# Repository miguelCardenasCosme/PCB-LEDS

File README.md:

# LEDs Payload PCB

LED array PCB for the optical downlink payload of the TEIDESAT-1 CubeSat.
The board emits modulated light pulses towards ground stations.

## Status

**v0.3** — layout complete, ready for manufacturing.
This version is intended to validate the predictions of the satellite's
transient thermal study.

## Design summary

- **LEDs:** 260 LEDs in 65 groups of 4 in series (12 V per group).
  Group placement was generated with an automated packing script,
  using line, L, Z, T and square group shapes.
- **Stackup (4 layers, top to bottom):** driver connectors / GND / 12V / LEDs.
- **Power distribution:** copper zones instead of tracks.
- **Vias:** through vias (blind vias were not available in the manufacturing process).
- **Connectors:** 5-pin (4-pin parts were out of stock). Required current capacity: 23 A.
- **Central opening:** leaves room for the optical board mounted behind.
- The LED driver is a separate PCB; it connects to this board through global connectors.

## Repository structure

- `hardware/` — KiCad project (schematic, PCB, project file and custom symbol/footprint/3D libraries).

Open with **KiCad 10.0.5** or newer.

## Open items / future versions

- Thermal: no copper changes for heat dissipation in v0.3. The board is planned
  to be mounted on an aluminium plate; check the risk of shorts through the through vias.

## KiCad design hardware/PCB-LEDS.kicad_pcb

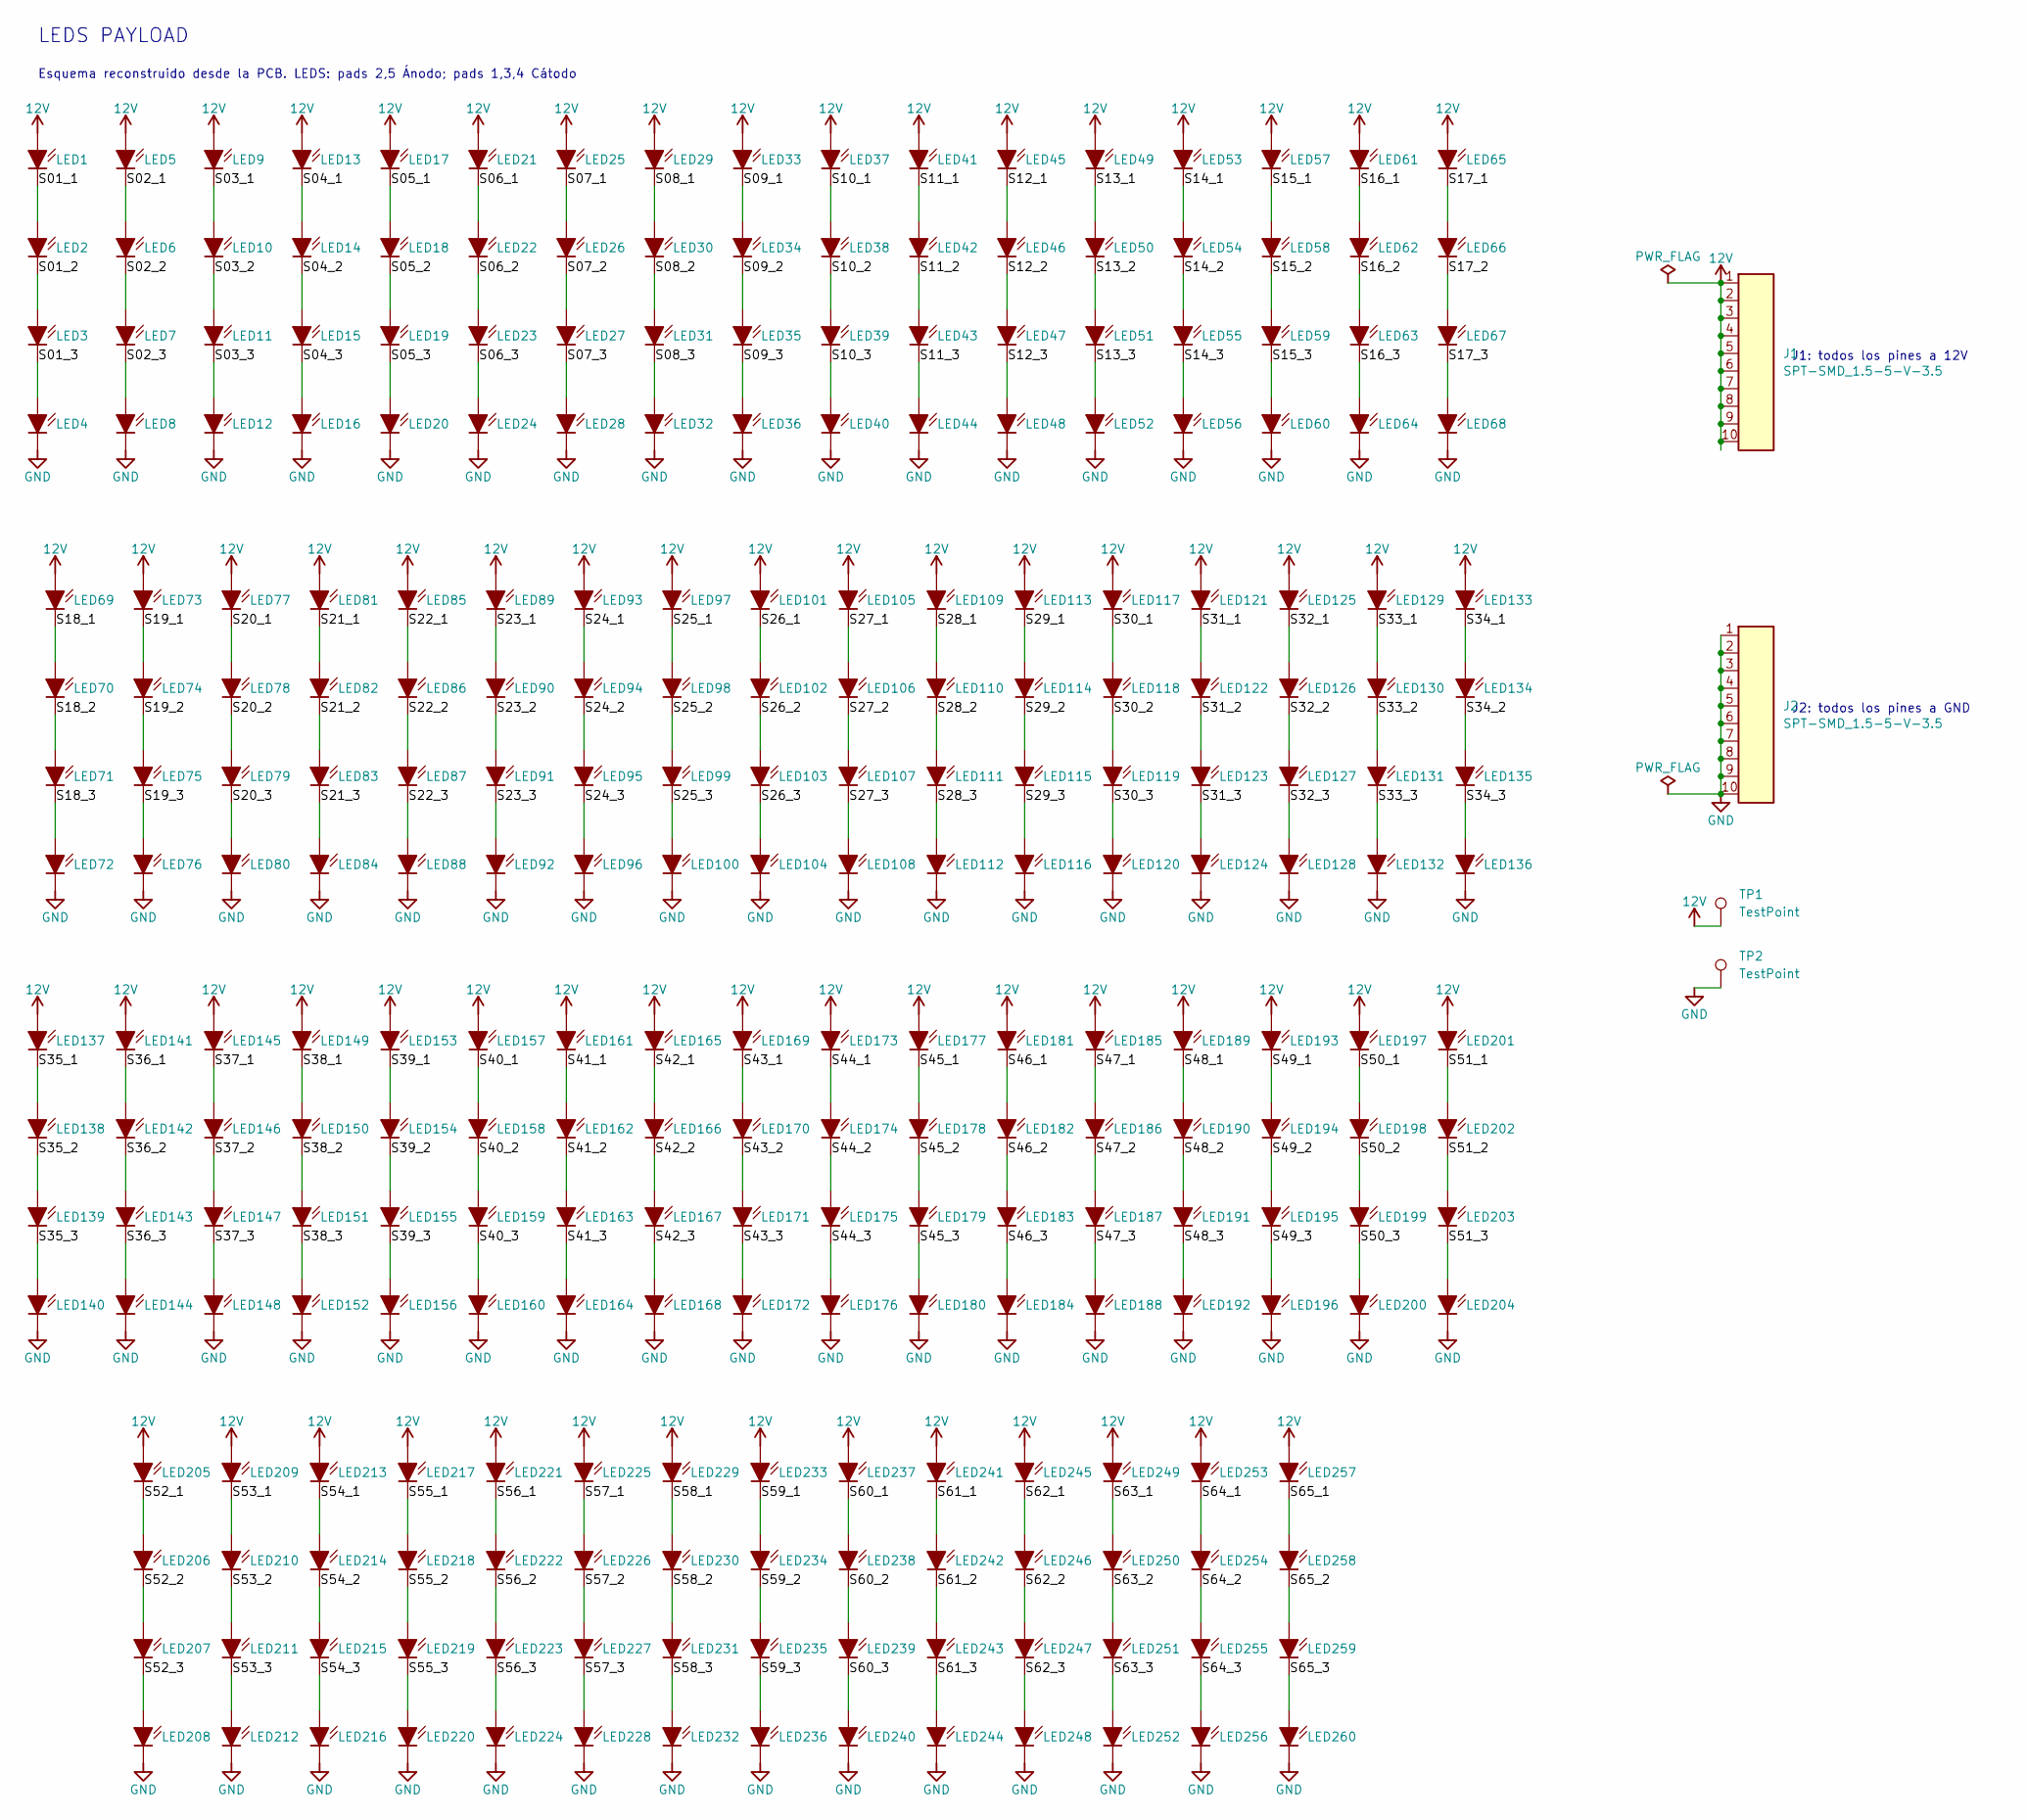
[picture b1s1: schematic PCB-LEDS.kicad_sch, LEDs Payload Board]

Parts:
J1, J2: SPT-SMD_1.5-5-V-3.5
LED1, LED2, LED3, LED4, LED5, LED6, LED7, LED8, LED9, LED10, LED11, LED12, LED13, LED14, LED15, LED16, LED17, LED18, LED19, LED20, LED21, LED22, LED23, LED24, LED25, LED26, LED27, LED28, LED29, LED30, LED31, LED32, LED33, LED34, LED35, LED36, LED37, LED38, LED39, LED40, LED41, LED42, LED43, LED44, LED45, LED46, LED47, LED48, LED49, LED50, LED51, LED52, LED53, LED54, LED55, LED56, LED57, LED58, LED59, LED60, LED61, LED62, LED63, LED64, LED65, LED66, LED67, LED68, LED69, LED70, LED71, LED72, LED73, LED74, LED75, LED76, LED77, LED78, LED79, LED80, LED81, LED82, LED83, LED84, LED85, LED86, LED87, LED88, LED89, LED90, LED91, LED92, LED93, LED94, LED95, LED96, LED97, LED98, LED99, LED100, LED101, LED102, LED103, LED104, LED105, LED106, LED107, LED108, LED109, LED110, LED111, LED112, LED113, LED114, LED115, LED116, LED117, LED118, LED119, LED120, LED121, LED122, LED123, LED124, LED125, LED126, LED127, LED128, LED129, LED130, LED131, LED132, LED133, LED134, LED135, LED136, LED137, LED138, LED139, LED140, LED141, LED142, LED143, LED144, LED145, LED146, LED147, LED148, LED149, LED150, LED151, LED152, LED153, LED154, LED155, LED156, LED157, LED158, LED159, LED160, LED161, LED162, LED163, LED164, LED165, LED166, LED167, LED168, LED169, LED170, LED171, LED172, LED173, LED174, LED175, LED176, LED177, LED178, LED179, LED180, LED181, LED182, LED183, LED184, LED185, LED186, LED187, LED188, LED189, LED190, LED191, LED192, LED193, LED194, LED195, LED196, LED197, LED198, LED199, LED200, LED201, LED202, LED203, LED204, LED205, LED206, LED207, LED208, LED209, LED210, LED211, LED212, LED213, LED214, LED215, LED216, LED217, LED218, LED219, LED220, LED221, LED222, LED223, LED224, LED225, LED226, LED227, LED228, LED229, LED230, LED231, LED232, LED233, LED234, LED235, LED236, LED237, LED238, LED239, LED240, LED241, LED242, LED243, LED244, LED245, LED246, LED247, LED248, LED249, LED250, LED251, LED252, LED253, LED254, LED255, LED256, LED257, LED258, LED259, LED260: KW_DMLQ33.SG
TP1, TP2: TestPoint; TestPoint_Pad_D1.5mm

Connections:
12V: J1.1, J1.2, J1.3, J1.4, J1.5, J1.6, J1.7, J1.8, J1.9, J1.10, LED1.2 (A), LED1.5 (A), LED5.2 (A), LED5.5 (A), LED9.2 (A), LED9.5 (A), LED13.2 (A), LED13.5 (A), LED17.2 (A), LED17.5 (A), LED21.2 (A), LED21.5 (A), LED25.2 (A), LED25.5 (A), LED29.2 (A), LED29.5 (A), LED33.2 (A), LED33.5 (A), LED37.2 (A), LED37.5 (A), LED41.2 (A), LED41.5 (A), LED45.2 (A), LED45.5 (A), LED49.2 (A), LED49.5 (A), LED53.2 (A), LED53.5 (A), LED57.2 (A), LED57.5 (A), LED61.2 (A), LED61.5 (A), LED65.2 (A), LED65.5 (A), LED69.2 (A), LED69.5 (A), LED73.2 (A), LED73.5 (A), LED77.2 (A), LED77.5 (A), LED81.2 (A), LED81.5 (A), LED85.2 (A), LED85.5 (A), LED89.2 (A), LED89.5 (A), LED93.2 (A), LED93.5 (A), LED97.2 (A), LED97.5 (A), LED101.2 (A), LED101.5 (A), LED105.2 (A), LED105.5 (A), LED109.2 (A), LED109.5 (A), LED113.2 (A), LED113.5 (A), LED117.2 (A), LED117.5 (A), LED121.2 (A), LED121.5 (A), LED125.2 (A), LED125.5 (A), LED129.2 (A), LED129.5 (A), LED133.2 (A), LED133.5 (A), LED137.2 (A), LED137.5 (A), LED141.2 (A), LED141.5 (A), LED145.2 (A), LED145.5 (A), LED149.2 (A), LED149.5 (A), LED153.2 (A), LED153.5 (A), LED157.2 (A), LED157.5 (A), LED161.2 (A), LED161.5 (A), LED165.2 (A), LED165.5 (A), LED169.2 (A), LED169.5 (A), LED173.2 (A), LED173.5 (A), LED177.2 (A), LED177.5 (A), LED181.2 (A), LED181.5 (A), LED185.2 (A), LED185.5 (A), LED189.2 (A), LED189.5 (A), LED193.2 (A), LED193.5 (A), LED197.2 (A), LED197.5 (A), LED201.2 (A), LED201.5 (A), LED205.2 (A), LED205.5 (A), LED209.2 (A), LED209.5 (A), LED213.2 (A), LED213.5 (A), LED217.2 (A), LED217.5 (A), LED221.2 (A), LED221.5 (A), LED225.2 (A), LED225.5 (A), LED229.2 (A), LED229.5 (A), LED233.2 (A), LED233.5 (A), LED237.2 (A), LED237.5 (A), LED241.2 (A), LED241.5 (A), LED245.2 (A), LED245.5 (A), LED249.2 (A), LED249.5 (A), LED253.2 (A), LED253.5 (A), LED257.2 (A), LED257.5 (A), TP1.1 (1_1)
/S01_1: LED1.1 (K), LED1.3 (K), LED1.4 (K), LED2.2 (A), LED2.5 (A)
/S01_2: LED2.1 (K), LED2.3 (K), LED2.4 (K), LED3.2 (A), LED3.5 (A)
/S01_3: LED3.1 (K), LED3.3 (K), LED3.4 (K), LED4.2 (A), LED4.5 (A)
/S02_1: LED5.1 (K), LED5.3 (K), LED5.4 (K), LED6.2 (A), LED6.5 (A)
/S02_2: LED6.1 (K), LED6.3 (K), LED6.4 (K), LED7.2 (A), LED7.5 (A)
/S02_3: LED7.1 (K), LED7.3 (K), LED7.4 (K), LED8.2 (A), LED8.5 (A)
/S03_1: LED9.1 (K), LED9.3 (K), LED9.4 (K), LED10.2 (A), LED10.5 (A)
/S03_2: LED10.1 (K), LED10.3 (K), LED10.4 (K), LED11.2 (A), LED11.5 (A)
/S03_3: LED11.1 (K), LED11.3 (K), LED11.4 (K), LED12.2 (A), LED12.5 (A)
/S04_1: LED13.1 (K), LED13.3 (K), LED13.4 (K), LED14.2 (A), LED14.5 (A)
/S04_2: LED14.1 (K), LED14.3 (K), LED14.4 (K), LED15.2 (A), LED15.5 (A)
/S04_3: LED15.1 (K), LED15.3 (K), LED15.4 (K), LED16.2 (A), LED16.5 (A)
/S05_1: LED17.1 (K), LED17.3 (K), LED17.4 (K), LED18.2 (A), LED18.5 (A)
/S05_2: LED18.1 (K), LED18.3 (K), LED18.4 (K), LED19.2 (A), LED19.5 (A)
/S05_3: LED19.1 (K), LED19.3 (K), LED19.4 (K), LED20.2 (A), LED20.5 (A)
/S06_1: LED21.1 (K), LED21.3 (K), LED21.4 (K), LED22.2 (A), LED22.5 (A)
/S06_2: LED22.1 (K), LED22.3 (K), LED22.4 (K), LED23.2 (A), LED23.5 (A)
/S06_3: LED23.1 (K), LED23.3 (K), LED23.4 (K), LED24.2 (A), LED24.5 (A)
/S07_1: LED25.1 (K), LED25.3 (K), LED25.4 (K), LED26.2 (A), LED26.5 (A)
/S07_2: LED26.1 (K), LED26.3 (K), LED26.4 (K), LED27.2 (A), LED27.5 (A)
/S07_3: LED27.1 (K), LED27.3 (K), LED27.4 (K), LED28.2 (A), LED28.5 (A)
/S08_1: LED29.1 (K), LED29.3 (K), LED29.4 (K), LED30.2 (A), LED30.5 (A)
/S08_2: LED30.1 (K), LED30.3 (K), LED30.4 (K), LED31.2 (A), LED31.5 (A)
/S08_3: LED31.1 (K), LED31.3 (K), LED31.4 (K), LED32.2 (A), LED32.5 (A)
/S09_1: LED33.1 (K), LED33.3 (K), LED33.4 (K), LED34.2 (A), LED34.5 (A)
/S09_2: LED34.1 (K), LED34.3 (K), LED34.4 (K), LED35.2 (A), LED35.5 (A)
/S09_3: LED35.1 (K), LED35.3 (K), LED35.4 (K), LED36.2 (A), LED36.5 (A)
/S10_1: LED37.1 (K), LED37.3 (K), LED37.4 (K), LED38.2 (A), LED38.5 (A)
/S10_2: LED38.1 (K), LED38.3 (K), LED38.4 (K), LED39.2 (A), LED39.5 (A)
/S10_3: LED39.1 (K), LED39.3 (K), LED39.4 (K), LED40.2 (A), LED40.5 (A)
/S11_1: LED41.1 (K), LED41.3 (K), LED41.4 (K), LED42.2 (A), LED42.5 (A)
/S11_2: LED42.1 (K), LED42.3 (K), LED42.4 (K), LED43.2 (A), LED43.5 (A)
/S11_3: LED43.1 (K), LED43.3 (K), LED43.4 (K), LED44.2 (A), LED44.5 (A)
/S12_1: LED45.1 (K), LED45.3 (K), LED45.4 (K), LED46.2 (A), LED46.5 (A)
/S12_2: LED46.1 (K), LED46.3 (K), LED46.4 (K), LED47.2 (A), LED47.5 (A)
/S12_3: LED47.1 (K), LED47.3 (K), LED47.4 (K), LED48.2 (A), LED48.5 (A)
/S13_1: LED49.1 (K), LED49.3 (K), LED49.4 (K), LED50.2 (A), LED50.5 (A)
/S13_2: LED50.1 (K), LED50.3 (K), LED50.4 (K), LED51.2 (A), LED51.5 (A)
/S13_3: LED51.1 (K), LED51.3 (K), LED51.4 (K), LED52.2 (A), LED52.5 (A)
/S14_1: LED53.1 (K), LED53.3 (K), LED53.4 (K), LED54.2 (A), LED54.5 (A)
/S14_2: LED54.1 (K), LED54.3 (K), LED54.4 (K), LED55.2 (A), LED55.5 (A)
/S14_3: LED55.1 (K), LED55.3 (K), LED55.4 (K), LED56.2 (A), LED56.5 (A)
/S15_1: LED57.1 (K), LED57.3 (K), LED57.4 (K), LED58.2 (A), LED58.5 (A)
/S15_2: LED58.1 (K), LED58.3 (K), LED58.4 (K), LED59.2 (A), LED59.5 (A)
/S15_3: LED59.1 (K), LED59.3 (K), LED59.4 (K), LED60.2 (A), LED60.5 (A)
/S16_1: LED61.1 (K), LED61.3 (K), LED61.4 (K), LED62.2 (A), LED62.5 (A)
/S16_2: LED62.1 (K), LED62.3 (K), LED62.4 (K), LED63.2 (A), LED63.5 (A)
/S16_3: LED63.1 (K), LED63.3 (K), LED63.4 (K), LED64.2 (A), LED64.5 (A)
/S17_1: LED65.1 (K), LED65.3 (K), LED65.4 (K), LED66.2 (A), LED66.5 (A)
/S17_2: LED66.1 (K), LED66.3 (K), LED66.4 (K), LED67.2 (A), LED67.5 (A)
/S17_3: LED67.1 (K), LED67.3 (K), LED67.4 (K), LED68.2 (A), LED68.5 (A)
/S18_1: LED69.1 (K), LED69.3 (K), LED69.4 (K), LED70.2 (A), LED70.5 (A)
/S18_2: LED70.1 (K), LED70.3 (K), LED70.4 (K), LED71.2 (A), LED71.5 (A)
/S18_3: LED71.1 (K), LED71.3 (K), LED71.4 (K), LED72.2 (A), LED72.5 (A)
/S19_1: LED73.1 (K), LED73.3 (K), LED73.4 (K), LED74.2 (A), LED74.5 (A)
/S19_2: LED74.1 (K), LED74.3 (K), LED74.4 (K), LED75.2 (A), LED75.5 (A)
/S19_3: LED75.1 (K), LED75.3 (K), LED75.4 (K), LED76.2 (A), LED76.5 (A)
/S20_1: LED77.1 (K), LED77.3 (K), LED77.4 (K), LED78.2 (A), LED78.5 (A)
/S20_2: LED78.1 (K), LED78.3 (K), LED78.4 (K), LED79.2 (A), LED79.5 (A)
/S20_3: LED79.1 (K), LED79.3 (K), LED79.4 (K), LED80.2 (A), LED80.5 (A)
/S21_1: LED81.1 (K), LED81.3 (K), LED81.4 (K), LED82.2 (A), LED82.5 (A)
/S21_2: LED82.1 (K), LED82.3 (K), LED82.4 (K), LED83.2 (A), LED83.5 (A)
/S21_3: LED83.1 (K), LED83.3 (K), LED83.4 (K), LED84.2 (A), LED84.5 (A)
/S22_1: LED85.1 (K), LED85.3 (K), LED85.4 (K), LED86.2 (A), LED86.5 (A)
/S22_2: LED86.1 (K), LED86.3 (K), LED86.4 (K), LED87.2 (A), LED87.5 (A)
/S22_3: LED87.1 (K), LED87.3 (K), LED87.4 (K), LED88.2 (A), LED88.5 (A)
/S23_1: LED89.1 (K), LED89.3 (K), LED89.4 (K), LED90.2 (A), LED90.5 (A)
/S23_2: LED90.1 (K), LED90.3 (K), LED90.4 (K), LED91.2 (A), LED91.5 (A)
/S23_3: LED91.1 (K), LED91.3 (K), LED91.4 (K), LED92.2 (A), LED92.5 (A)
/S24_1: LED93.1 (K), LED93.3 (K), LED93.4 (K), LED94.2 (A), LED94.5 (A)
/S24_2: LED94.1 (K), LED94.3 (K), LED94.4 (K), LED95.2 (A), LED95.5 (A)
/S24_3: LED95.1 (K), LED95.3 (K), LED95.4 (K), LED96.2 (A), LED96.5 (A)
/S25_1: LED97.1 (K), LED97.3 (K), LED97.4 (K), LED98.2 (A), LED98.5 (A)
/S25_2: LED98.1 (K), LED98.3 (K), LED98.4 (K), LED99.2 (A), LED99.5 (A)
/S25_3: LED99.1 (K), LED99.3 (K), LED99.4 (K), LED100.2 (A), LED100.5 (A)
/S26_1: LED101.1 (K), LED101.3 (K), LED101.4 (K), LED102.2 (A), LED102.5 (A)
/S26_2: LED102.1 (K), LED102.3 (K), LED102.4 (K), LED103.2 (A), LED103.5 (A)
/S26_3: LED103.1 (K), LED103.3 (K), LED103.4 (K), LED104.2 (A), LED104.5 (A)
/S27_1: LED105.1 (K), LED105.3 (K), LED105.4 (K), LED106.2 (A), LED106.5 (A)
/S27_2: LED106.1 (K), LED106.3 (K), LED106.4 (K), LED107.2 (A), LED107.5 (A)
/S27_3: LED107.1 (K), LED107.3 (K), LED107.4 (K), LED108.2 (A), LED108.5 (A)
/S28_1: LED109.1 (K), LED109.3 (K), LED109.4 (K), LED110.2 (A), LED110.5 (A)
/S28_2: LED110.1 (K), LED110.3 (K), LED110.4 (K), LED111.2 (A), LED111.5 (A)
/S28_3: LED111.1 (K), LED111.3 (K), LED111.4 (K), LED112.2 (A), LED112.5 (A)
/S29_1: LED113.1 (K), LED113.3 (K), LED113.4 (K), LED114.2 (A), LED114.5 (A)
/S29_2: LED114.1 (K), LED114.3 (K), LED114.4 (K), LED115.2 (A), LED115.5 (A)
/S29_3: LED115.1 (K), LED115.3 (K), LED115.4 (K), LED116.2 (A), LED116.5 (A)
/S30_1: LED117.1 (K), LED117.3 (K), LED117.4 (K), LED118.2 (A), LED118.5 (A)
/S30_2: LED118.1 (K), LED118.3 (K), LED118.4 (K), LED119.2 (A), LED119.5 (A)
/S30_3: LED119.1 (K), LED119.3 (K), LED119.4 (K), LED120.2 (A), LED120.5 (A)
/S31_1: LED121.1 (K), LED121.3 (K), LED121.4 (K), LED122.2 (A), LED122.5 (A)
/S31_2: LED122.1 (K), LED122.3 (K), LED122.4 (K), LED123.2 (A), LED123.5 (A)
/S31_3: LED123.1 (K), LED123.3 (K), LED123.4 (K), LED124.2 (A), LED124.5 (A)
/S32_1: LED125.1 (K), LED125.3 (K), LED125.4 (K), LED126.2 (A), LED126.5 (A)
/S32_2: LED126.1 (K), LED126.3 (K), LED126.4 (K), LED127.2 (A), LED127.5 (A)
/S32_3: LED127.1 (K), LED127.3 (K), LED127.4 (K), LED128.2 (A), LED128.5 (A)
/S33_1: LED129.1 (K), LED129.3 (K), LED129.4 (K), LED130.2 (A), LED130.5 (A)
/S33_2: LED130.1 (K), LED130.3 (K), LED130.4 (K), LED131.2 (A), LED131.5 (A)
/S33_3: LED131.1 (K), LED131.3 (K), LED131.4 (K), LED132.2 (A), LED132.5 (A)
/S34_1: LED133.1 (K), LED133.3 (K), LED133.4 (K), LED134.2 (A), LED134.5 (A)
/S34_2: LED134.1 (K), LED134.3 (K), LED134.4 (K), LED135.2 (A), LED135.5 (A)
/S34_3: LED135.1 (K), LED135.3 (K), LED135.4 (K), LED136.2 (A), LED136.5 (A)
/S35_1: LED137.1 (K), LED137.3 (K), LED137.4 (K), LED138.2 (A), LED138.5 (A)
/S35_2: LED138.1 (K), LED138.3 (K), LED138.4 (K), LED139.2 (A), LED139.5 (A)
/S35_3: LED139.1 (K), LED139.3 (K), LED139.4 (K), LED140.2 (A), LED140.5 (A)
/S36_1: LED141.1 (K), LED141.3 (K), LED141.4 (K), LED142.2 (A), LED142.5 (A)
/S36_2: LED142.1 (K), LED142.3 (K), LED142.4 (K), LED143.2 (A), LED143.5 (A)
/S36_3: LED143.1 (K), LED143.3 (K), LED143.4 (K), LED144.2 (A), LED144.5 (A)
/S37_1: LED145.1 (K), LED145.3 (K), LED145.4 (K), LED146.2 (A), LED146.5 (A)
/S37_2: LED146.1 (K), LED146.3 (K), LED146.4 (K), LED147.2 (A), LED147.5 (A)
/S37_3: LED147.1 (K), LED147.3 (K), LED147.4 (K), LED148.2 (A), LED148.5 (A)
/S38_1: LED149.1 (K), LED149.3 (K), LED149.4 (K), LED150.2 (A), LED150.5 (A)
/S38_2: LED150.1 (K), LED150.3 (K), LED150.4 (K), LED151.2 (A), LED151.5 (A)
/S38_3: LED151.1 (K), LED151.3 (K), LED151.4 (K), LED152.2 (A), LED152.5 (A)
/S39_1: LED153.1 (K), LED153.3 (K), LED153.4 (K), LED154.2 (A), LED154.5 (A)
/S39_2: LED154.1 (K), LED154.3 (K), LED154.4 (K), LED155.2 (A), LED155.5 (A)
/S39_3: LED155.1 (K), LED155.3 (K), LED155.4 (K), LED156.2 (A), LED156.5 (A)
/S40_1: LED157.1 (K), LED157.3 (K), LED157.4 (K), LED158.2 (A), LED158.5 (A)
/S40_2: LED158.1 (K), LED158.3 (K), LED158.4 (K), LED159.2 (A), LED159.5 (A)
/S40_3: LED159.1 (K), LED159.3 (K), LED159.4 (K), LED160.2 (A), LED160.5 (A)
/S41_1: LED161.1 (K), LED161.3 (K), LED161.4 (K), LED162.2 (A), LED162.5 (A)
/S41_2: LED162.1 (K), LED162.3 (K), LED162.4 (K), LED163.2 (A), LED163.5 (A)
/S41_3: LED163.1 (K), LED163.3 (K), LED163.4 (K), LED164.2 (A), LED164.5 (A)
/S42_1: LED165.1 (K), LED165.3 (K), LED165.4 (K), LED166.2 (A), LED166.5 (A)
/S42_2: LED166.1 (K), LED166.3 (K), LED166.4 (K), LED167.2 (A), LED167.5 (A)
/S42_3: LED167.1 (K), LED167.3 (K), LED167.4 (K), LED168.2 (A), LED168.5 (A)
/S43_1: LED169.1 (K), LED169.3 (K), LED169.4 (K), LED170.2 (A), LED170.5 (A)
/S43_2: LED170.1 (K), LED170.3 (K), LED170.4 (K), LED171.2 (A), LED171.5 (A)
/S43_3: LED171.1 (K), LED171.3 (K), LED171.4 (K), LED172.2 (A), LED172.5 (A)
/S44_1: LED173.1 (K), LED173.3 (K), LED173.4 (K), LED174.2 (A), LED174.5 (A)
/S44_2: LED174.1 (K), LED174.3 (K), LED174.4 (K), LED175.2 (A), LED175.5 (A)
/S44_3: LED175.1 (K), LED175.3 (K), LED175.4 (K), LED176.2 (A), LED176.5 (A)
/S45_1: LED177.1 (K), LED177.3 (K), LED177.4 (K), LED178.2 (A), LED178.5 (A)
/S45_2: LED178.1 (K), LED178.3 (K), LED178.4 (K), LED179.2 (A), LED179.5 (A)
/S45_3: LED179.1 (K), LED179.3 (K), LED179.4 (K), LED180.2 (A), LED180.5 (A)
/S46_1: LED181.1 (K), LED181.3 (K), LED181.4 (K), LED182.2 (A), LED182.5 (A)
/S46_2: LED182.1 (K), LED182.3 (K), LED182.4 (K), LED183.2 (A), LED183.5 (A)
/S46_3: LED183.1 (K), LED183.3 (K), LED183.4 (K), LED184.2 (A), LED184.5 (A)
/S47_1: LED185.1 (K), LED185.3 (K), LED185.4 (K), LED186.2 (A), LED186.5 (A)
/S47_2: LED186.1 (K), LED186.3 (K), LED186.4 (K), LED187.2 (A), LED187.5 (A)
/S47_3: LED187.1 (K), LED187.3 (K), LED187.4 (K), LED188.2 (A), LED188.5 (A)
/S48_1: LED189.1 (K), LED189.3 (K), LED189.4 (K), LED190.2 (A), LED190.5 (A)
/S48_2: LED190.1 (K), LED190.3 (K), LED190.4 (K), LED191.2 (A), LED191.5 (A)
/S48_3: LED191.1 (K), LED191.3 (K), LED191.4 (K), LED192.2 (A), LED192.5 (A)
/S49_1: LED193.1 (K), LED193.3 (K), LED193.4 (K), LED194.2 (A), LED194.5 (A)
/S49_2: LED194.1 (K), LED194.3 (K), LED194.4 (K), LED195.2 (A), LED195.5 (A)
/S49_3: LED195.1 (K), LED195.3 (K), LED195.4 (K), LED196.2 (A), LED196.5 (A)
/S50_1: LED197.1 (K), LED197.3 (K), LED197.4 (K), LED198.2 (A), LED198.5 (A)
/S50_2: LED198.1 (K), LED198.3 (K), LED198.4 (K), LED199.2 (A), LED199.5 (A)
/S50_3: LED199.1 (K), LED199.3 (K), LED199.4 (K), LED200.2 (A), LED200.5 (A)
/S51_1: LED201.1 (K), LED201.3 (K), LED201.4 (K), LED202.2 (A), LED202.5 (A)
/S51_2: LED202.1 (K), LED202.3 (K), LED202.4 (K), LED203.2 (A), LED203.5 (A)
/S51_3: LED203.1 (K), LED203.3 (K), LED203.4 (K), LED204.2 (A), LED204.5 (A)
/S52_1: LED205.1 (K), LED205.3 (K), LED205.4 (K), LED206.2 (A), LED206.5 (A)
/S52_2: LED206.1 (K), LED206.3 (K), LED206.4 (K), LED207.2 (A), LED207.5 (A)
/S52_3: LED207.1 (K), LED207.3 (K), LED207.4 (K), LED208.2 (A), LED208.5 (A)
/S53_1: LED209.1 (K), LED209.3 (K), LED209.4 (K), LED210.2 (A), LED210.5 (A)
/S53_2: LED210.1 (K), LED210.3 (K), LED210.4 (K), LED211.2 (A), LED211.5 (A)
/S53_3: LED211.1 (K), LED211.3 (K), LED211.4 (K), LED212.2 (A), LED212.5 (A)
/S54_1: LED213.1 (K), LED213.3 (K), LED213.4 (K), LED214.2 (A), LED214.5 (A)
/S54_2: LED214.1 (K), LED214.3 (K), LED214.4 (K), LED215.2 (A), LED215.5 (A)
/S54_3: LED215.1 (K), LED215.3 (K), LED215.4 (K), LED216.2 (A), LED216.5 (A)
/S55_1: LED217.1 (K), LED217.3 (K), LED217.4 (K), LED218.2 (A), LED218.5 (A)
/S55_2: LED218.1 (K), LED218.3 (K), LED218.4 (K), LED219.2 (A), LED219.5 (A)
/S55_3: LED219.1 (K), LED219.3 (K), LED219.4 (K), LED220.2 (A), LED220.5 (A)
/S56_1: LED221.1 (K), LED221.3 (K), LED221.4 (K), LED222.2 (A), LED222.5 (A)
/S56_2: LED222.1 (K), LED222.3 (K), LED222.4 (K), LED223.2 (A), LED223.5 (A)
/S56_3: LED223.1 (K), LED223.3 (K), LED223.4 (K), LED224.2 (A), LED224.5 (A)
/S57_1: LED225.1 (K), LED225.3 (K), LED225.4 (K), LED226.2 (A), LED226.5 (A)
/S57_2: LED226.1 (K), LED226.3 (K), LED226.4 (K), LED227.2 (A), LED227.5 (A)
/S57_3: LED227.1 (K), LED227.3 (K), LED227.4 (K), LED228.2 (A), LED228.5 (A)
/S58_1: LED229.1 (K), LED229.3 (K), LED229.4 (K), LED230.2 (A), LED230.5 (A)
/S58_2: LED230.1 (K), LED230.3 (K), LED230.4 (K), LED231.2 (A), LED231.5 (A)
/S58_3: LED231.1 (K), LED231.3 (K), LED231.4 (K), LED232.2 (A), LED232.5 (A)
/S59_1: LED233.1 (K), LED233.3 (K), LED233.4 (K), LED234.2 (A), LED234.5 (A)
/S59_2: LED234.1 (K), LED234.3 (K), LED234.4 (K), LED235.2 (A), LED235.5 (A)
/S59_3: LED235.1 (K), LED235.3 (K), LED235.4 (K), LED236.2 (A), LED236.5 (A)
/S60_1: LED237.1 (K), LED237.3 (K), LED237.4 (K), LED238.2 (A), LED238.5 (A)
/S60_2: LED238.1 (K), LED238.3 (K), LED238.4 (K), LED239.2 (A), LED239.5 (A)
/S60_3: LED239.1 (K), LED239.3 (K), LED239.4 (K), LED240.2 (A), LED240.5 (A)
/S61_1: LED241.1 (K), LED241.3 (K), LED241.4 (K), LED242.2 (A), LED242.5 (A)
/S61_2: LED242.1 (K), LED242.3 (K), LED242.4 (K), LED243.2 (A), LED243.5 (A)
/S61_3: LED243.1 (K), LED243.3 (K), LED243.4 (K), LED244.2 (A), LED244.5 (A)
/S62_1: LED245.1 (K), LED245.3 (K), LED245.4 (K), LED246.2 (A), LED246.5 (A)
/S62_2: LED246.1 (K), LED246.3 (K), LED246.4 (K), LED247.2 (A), LED247.5 (A)
/S62_3: LED247.1 (K), LED247.3 (K), LED247.4 (K), LED248.2 (A), LED248.5 (A)
/S63_1: LED249.1 (K), LED249.3 (K), LED249.4 (K), LED250.2 (A), LED250.5 (A)
/S63_2: LED250.1 (K), LED250.3 (K), LED250.4 (K), LED251.2 (A), LED251.5 (A)
/S63_3: LED251.1 (K), LED251.3 (K), LED251.4 (K), LED252.2 (A), LED252.5 (A)
/S64_1: LED253.1 (K), LED253.3 (K), LED253.4 (K), LED254.2 (A), LED254.5 (A)
/S64_2: LED254.1 (K), LED254.3 (K), LED254.4 (K), LED255.2 (A), LED255.5 (A)
/S64_3: LED255.1 (K), LED255.3 (K), LED255.4 (K), LED256.2 (A), LED256.5 (A)
/S65_1: LED257.1 (K), LED257.3 (K), LED257.4 (K), LED258.2 (A), LED258.5 (A)
/S65_2: LED258.1 (K), LED258.3 (K), LED258.4 (K), LED259.2 (A), LED259.5 (A)
/S65_3: LED259.1 (K), LED259.3 (K), LED259.4 (K), LED260.2 (A), LED260.5 (A)
GND: J2.1, J2.2, J2.3, J2.4, J2.5, J2.6, J2.7, J2.8, J2.9, J2.10, LED4.1 (K), LED4.3 (K), LED4.4 (K), LED8.1 (K), LED8.3 (K), LED8.4 (K), LED12.1 (K), LED12.3 (K), LED12.4 (K), LED16.1 (K), LED16.3 (K), LED16.4 (K), LED20.1 (K), LED20.3 (K), LED20.4 (K), LED24.1 (K), LED24.3 (K), LED24.4 (K), LED28.1 (K), LED28.3 (K), LED28.4 (K), LED32.1 (K), LED32.3 (K), LED32.4 (K), LED36.1 (K), LED36.3 (K), LED36.4 (K), LED40.1 (K), LED40.3 (K), LED40.4 (K), LED44.1 (K), LED44.3 (K), LED44.4 (K), LED48.1 (K), LED48.3 (K), LED48.4 (K), LED52.1 (K), LED52.3 (K), LED52.4 (K), LED56.1 (K), LED56.3 (K), LED56.4 (K), LED60.1 (K), LED60.3 (K), LED60.4 (K), LED64.1 (K), LED64.3 (K), LED64.4 (K), LED68.1 (K), LED68.3 (K), LED68.4 (K), LED72.1 (K), LED72.3 (K), LED72.4 (K), LED76.1 (K), LED76.3 (K), LED76.4 (K), LED80.1 (K), LED80.3 (K), LED80.4 (K), LED84.1 (K), LED84.3 (K), LED84.4 (K), LED88.1 (K), LED88.3 (K), LED88.4 (K), LED92.1 (K), LED92.3 (K), LED92.4 (K), LED96.1 (K), LED96.3 (K), LED96.4 (K), LED100.1 (K), LED100.3 (K), LED100.4 (K), LED104.1 (K), LED104.3 (K), LED104.4 (K), LED108.1 (K), LED108.3 (K), LED108.4 (K), LED112.1 (K), LED112.3 (K), LED112.4 (K), LED116.1 (K), LED116.3 (K), LED116.4 (K), LED120.1 (K), LED120.3 (K), LED120.4 (K), LED124.1 (K), LED124.3 (K), LED124.4 (K), LED128.1 (K), LED128.3 (K), LED128.4 (K), LED132.1 (K), LED132.3 (K), LED132.4 (K), LED136.1 (K), LED136.3 (K), LED136.4 (K), LED140.1 (K), LED140.3 (K), LED140.4 (K), LED144.1 (K), LED144.3 (K), LED144.4 (K), LED148.1 (K), LED148.3 (K), LED148.4 (K), LED152.1 (K), LED152.3 (K), LED152.4 (K), LED156.1 (K), LED156.3 (K), LED156.4 (K), LED160.1 (K), LED160.3 (K), LED160.4 (K), LED164.1 (K), LED164.3 (K), LED164.4 (K), LED168.1 (K), LED168.3 (K), LED168.4 (K), LED172.1 (K), LED172.3 (K), LED172.4 (K), LED176.1 (K), LED176.3 (K), LED176.4 (K), LED180.1 (K), LED180.3 (K), LED180.4 (K), LED184.1 (K), LED184.3 (K), LED184.4 (K), LED188.1 (K), LED188.3 (K), LED188.4 (K), LED192.1 (K), LED192.3 (K), LED192.4 (K), LED196.1 (K), LED196.3 (K), LED196.4 (K), LED200.1 (K), LED200.3 (K), LED200.4 (K), LED204.1 (K), LED204.3 (K), LED204.4 (K), LED208.1 (K), LED208.3 (K), LED208.4 (K), LED212.1 (K), LED212.3 (K), LED212.4 (K), LED216.1 (K), LED216.3 (K), LED216.4 (K), LED220.1 (K), LED220.3 (K), LED220.4 (K), LED224.1 (K), LED224.3 (K), LED224.4 (K), LED228.1 (K), LED228.3 (K), LED228.4 (K), LED232.1 (K), LED232.3 (K), LED232.4 (K), LED236.1 (K), LED236.3 (K), LED236.4 (K), LED240.1 (K), LED240.3 (K), LED240.4 (K), LED244.1 (K), LED244.3 (K), LED244.4 (K), LED248.1 (K), LED248.3 (K), LED248.4 (K), LED252.1 (K), LED252.3 (K), LED252.4 (K), LED256.1 (K), LED256.3 (K), LED256.4 (K), LED260.1 (K), LED260.3 (K), LED260.4 (K), TP2.1 (1_1)

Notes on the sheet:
J2: todos los pines a GND
LEDS PAYLOAD
Esquema reconstruido desde la PCB. LEDS: pads 2,5 Ánodo; pads 1,3,4 Cátodo
J1: todos los pines a 12V

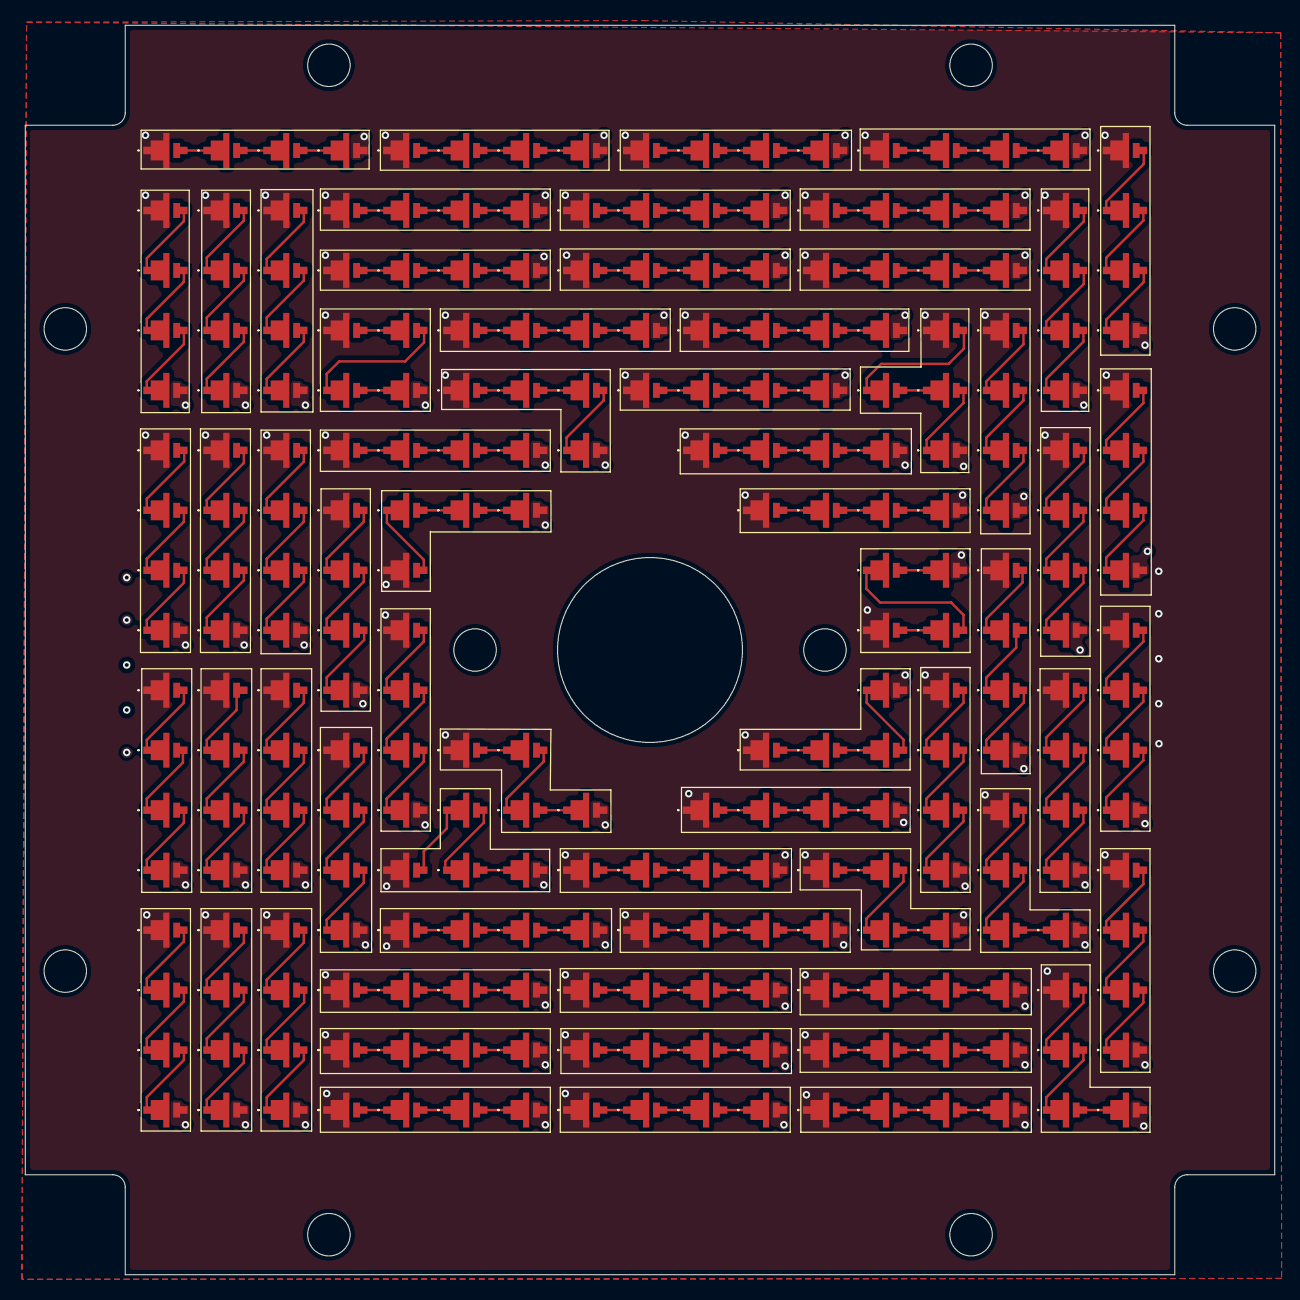
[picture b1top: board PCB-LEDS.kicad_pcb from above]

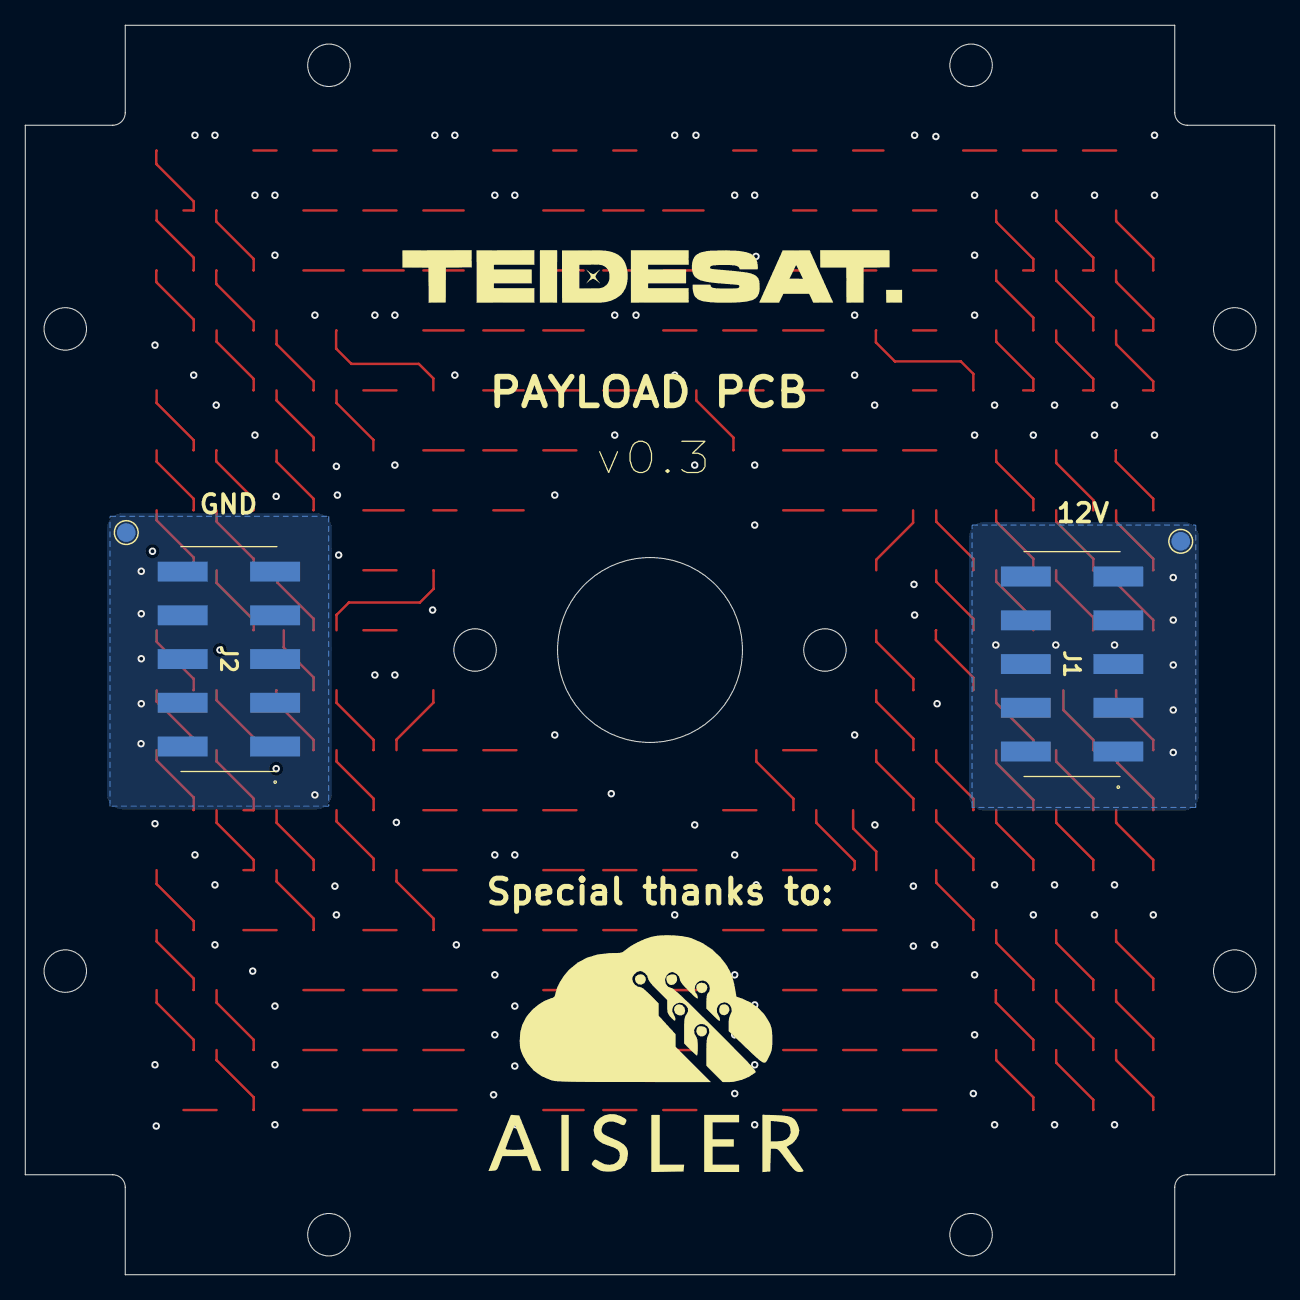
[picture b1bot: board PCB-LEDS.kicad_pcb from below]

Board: 4 copper layers, 100.0 x 100.0 mm, 264 parts (4 on the bottom side), 197 nets.
